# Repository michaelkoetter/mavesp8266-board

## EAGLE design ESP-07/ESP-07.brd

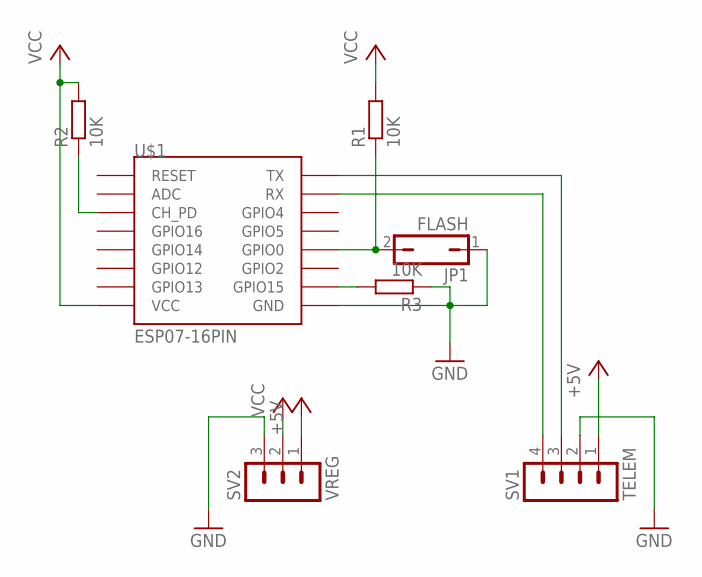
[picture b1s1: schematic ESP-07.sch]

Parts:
JP1: FLASH; JP1
R1, R2, R3: 10K; R0805
SV1: TELEM; MA04-1
SV2: VREG; MA03-1
U$1: ESP07-16PIN

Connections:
+5V: SV1.1, SV2.1
GND: JP1.1, R3.1, SV1.2, SV2.3, U$1.GND
unnamed: JP1.2, R1.1, U$1.GPIO0
unnamed: SV1.3, U$1.TX
unnamed: SV1.4, U$1.RX
unnamed: R3.2, U$1.GPIO15
unnamed: R2.1, U$1.CH_PD
VCC: R1.2, R2.2, SV2.2, U$1.VCC

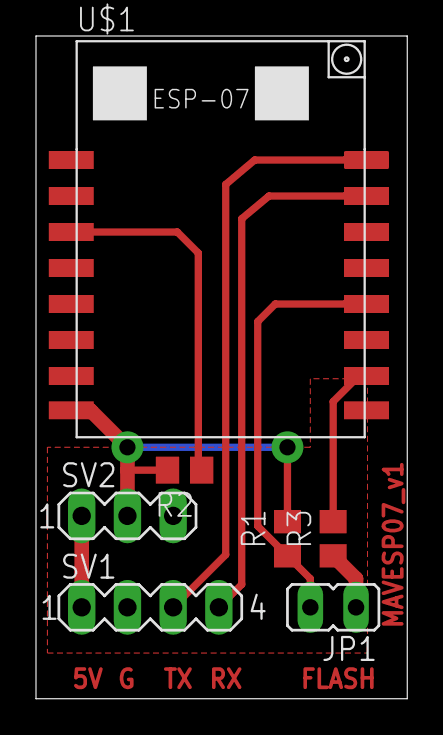
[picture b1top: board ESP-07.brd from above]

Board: 2 copper layers, 20.6 x 36.8 mm, 7 parts (0 on the bottom side), 8 nets.

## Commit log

2017-02-28 :tada: Added .gitattributes & .gitignore files
2017-02-28 initial design for ESP-07
2017-03-03 tweak layout
